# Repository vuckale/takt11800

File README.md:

# takt11800 - Compaq MX 11800 QMK/VIA Replacement PCB

Sponsored by PCBWay - [Read More](#pcbway)

This project is a **drop-in replacement PCB** designed for the **Compaq MX 11800**, also known as the **Cherry G80-11800** a classic mechanical keyboard featuring **Cherry MX Brown switches** and an integrated **trackball**.

Originally designed for use in server rooms and rack-mounted setups, the MX 11800's **compact, space-saving layout** made it a go-to choice in enterprise environments.

### Project Features

- **Powered by QMK Firmware** – Fully customizable keymaps, layers, macros, and lighting effects.
- **VIA Support** – Seamless configuration through the user-friendly VIA interface.
- **Trackball Support** – Full functionality for the integrated pointing device.
- **Drop-In Compatible** – No case modifications required. Designed to fit directly into the original shell and work with original components.
- **USB-C Connectivity** – Modern convenience and reliability.

### Known Issues

During testing, the integrated trackball worked reliably with some MX 11800 variants (based on testing with a single German layout unit), but showed intermittent or unreliable behavior on others (such as international-layout versions). In some cases, the trackball would work inconsistently or fail to initialize.

At the time of writing, no reliable software solution has been found. Based on the observed behavior and the available hardware information, it is suspected that this may be related to a voltage level mismatch. The MCU operates at 3.3 V logic, while the original trackball assembly may expect 5 V logic levels. This has not yet been conclusively confirmed and remains under investigation.

A revised PCB is planned to address this potential issue at the hardware level. Until then, builders should be aware that trackball functionality may vary depending on the specific keyboard and trackball assembly used.

### BOM and CPL Orientation

The included BOM (Bill of Materials) and CPL (Component Placement List) are provided for orientation purposes. Depending on the assembly options selected and any variations in components, you may need to adjust these files when placing your order to ensure correct assembly.

### Why This Project?

The original MX 11800 has aged gracefully, but its internals were due for a modern upgrade. This replacement PCB brings this legendary board into the modern era while preserving its unique charm and functionality.

Whether you're a retro keyboard enthusiast, a server admin with a soft spot for classic gear, or just someone who loves trackball keyboards, this project gives new life to an iconic piece of hardware.

# Layout

## Default Layout

This PCB supports multiple layout options. The previous image shows the default layout with colored keys and marked unit sizes that support alternate layouts. The default layout represents the configuration the keyboard is most commonly found in: ANSI enter with a 2.25u enter key, stepped caps lock, and a winkeyless 7u bottom row.

## Extended Layout

The extended layout adds support for additional four bottom row variations, which are marked on the image with the letters b–e. For easier assembly, these are also labeled on the PCB itself, with unit sizes marked next to the switch holes and a–e marked on the stabilizer holes. Additionally, the extended layout supports a non-stepped caps lock key, ISO enter, split left shift and a backspace and 2u shift that can be split into two 1u keys. The numpad can also be converted into a full 1u macropad.

## PCB Overview

## PCBWay

### Ordering Process

PCBWay made prototyping this PCB straightforward and easy. Their intuitive, beginner-friendly ordering process took all the guesswork out of manufacturing. I was impressed by how smoothly everything went, even on my first try. If you're curious to check it out or replicate the build, all the necessary files are neatly organized in the Fabrication Folder of this repository.

Following the steps on their interface, placing an order with PCBWay was easy. After uploading the Gerber .zip file, the platform pre-filled many default values suitable for my 2-layer PCB, simplifying the process significantly. The only manual customization I initially made was changing the solder mask color to black—a purely aesthetic choice. However, PCBWay offers a wide range of specification options for those who want more control.

You can choose between single pieces, customer-designed panels, or panels assembled by PCBWay, and even combine different PCB designs within a single panel. Layer configurations are highly flexible, ranging from 1 up to 14 layers, with support for advanced materials like FR-4, Aluminum, and Rogers for high-frequency or thermal applications. PCB thickness can be set anywhere from 0.2 mm up to 3.2 mm, and you can define track/spacing resolutions as fine as 3/3 mil. For higher durability or signal performance, different finished copper weights are also available—ranging from bare copper to 12 oz Cu.

Solder mask colors include not only standard options like green, red, and blue, but also premium finishes like matte black and matte green. Silkscreen printing supports multiple colors (white, black, yellow) and even UV multi-color printing. Additional advanced options include edge connectors, various surface finishes like ENIG, immersion silver, and ENEPIG, and via treatments such as tenting, plugging, or open vias.

You also have the option to remove PCBWay's product number for a small fee, specify custom FR4-TG ratings, and opt for specialized features like castellated holes, edge plating, or impedance control. With all these configuration options, PCBWay caters not only to hobbyists but also to professionals needing precise and high-performance PCBs.

For assembly, PCBWay provides a flexible set of options tailored to different needs: you can go with full turnkey assembly, where they source and solder everything; kitted/consigned, where you supply all the parts; or a combo option, where you send some components and let them handle the rest. 

For this project, I went with the full turnkey assembly—PCBWay not only assembled the boards but also sourced all the required components for me. This saved a huge amount of time and hassle, especially for parts that are hard to track down or have long lead times.

They also offer additional customization, like choosing whether to assemble single boards or panelized PCBs (recommended if you're doing runs of 20+ boards or working with small form factors), selecting top, bottom, or dual-sided assembly, and even specifying if you'd like to allow substitute components made in China—which I found useful for speeding up lead times without compromising quality.

Overall, their assembly service felt like a huge win—it was smooth, efficient, and let me focus entirely on design while they took care of the heavy lifting.

To do this, simply check the assembly option and fill in the necessary values as shown:

After clicking "Save to Cart," you can upload the BOM, CPL, and component placement orientation files to complete your order.

After placing the order, I had frequent and helpful communication with their engineering team, who reached out to clarify a few design decisions and even helped me correct some mistakes in my Gerber files. I really appreciated how responsive and collaborative they were—it felt like working with a partner, not just a service provider.

One particularly thoughtful touch was that before final assembly and shipping, they sent me high-resolution photos of the finished PCBs for confirmation. This gave me a last opportunity to visually inspect the boards and ensure everything looked right—a great quality-control step that added to my confidence in the process.

Throughout production, PCBWay provides visual order tracking on their website, which shows exactly where your order is at every stage—file review, fabrication, solder mask, silkscreen, assembly, testing, and packaging. It’s clearly laid out and updated in real time, which made the waiting process far less stressful.

The total turnaround time was about two weeks, which included fabrication, full assembly, and component sourcing. When the package arrived, it was clear that shipping was handled with care: each board was sealed in an anti-static bag, then carefully wrapped with protective shrink wrap and cushioning to prevent any damage during transit.

Overall, the combination of attentive support, visual transparency, and high-quality results made the whole experience smooth and satisfying. I wouldn’t hesitate to work with them again on future prototypes.

### Quality

This is where PCBWay truly shines. I was impressed by the overall PCB quality—the solder mask is perfectly uniform and consistent throughout. In my design, I included both silkscreen text and exposed copper text by selectively removing the top solder mask, and both came out flawless, with crisp details and no smudging or misalignment.

The components—including the MCU, SMD resistors, capacitors, and others—are perfectly placed, with flawless solder joints even on the tiniest parts. I’ll let the image speak for itself.

The plated through-holes on this PCB are clean, well-aligned, and have excellent copper coverage—perfect for reliable soldering. 

### Assembly

After soldering the switches and plugging in the trackball, all that was left was flashing the firmware. The STM32 chips come pre-flashed with a bootloader, so once connected to the PC, holding the BOOT switch and tapping NRST puts the board into flashing mode—simple as that.

The build includes 105 switches, and for a standard ISO layout, it uses 6× 2u stabilizers and 1× 7u stabilizer, though this may vary depending on the chosen layout.

### Final Words

Overall, working with PCBWay was a smooth and satisfying experience. The ordering process was easy, communication was fast and helpful, and the visual tracking kept me updated every step of the way. With a quick two-week turnaround, high-quality fabrication, flawless assembly, and great attention to detail, PCBWay delivered a professional result I’d gladly rely on again.

## License

This project is licensed under the **CERN Open Hardware Licence Version 2 - Strongly Reciprocal (CERN-OHL-S)**.

You are free to use, study, modify, and distribute the design files and products based on them, as long as any distributed modifications or derivative works are also released under the same license.

For the full license text, see the [LICENSE](LICENSE) file in this repository or visit the [official CERN OHL v2 page](https://gitlab.com/ohwr/project/cernohl/-/wikis/uploads/b236492596cfc91c12def7d50bbf7da0/cern_ohl_s_v2.pdf).

(C) 2025 [Aleksandar Vuckovic]

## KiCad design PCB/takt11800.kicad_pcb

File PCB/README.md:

# This is **Work In Progress**

Required **[Daughterboard repository](https://github.com:vuckale/va11800-daughterboard)**

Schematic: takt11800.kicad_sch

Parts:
BZ1: Buzzer; PinSocket_1x02_P2.00mm_Vertical
C8, C9: 1uF; Capacitor_0402; LCSC C52923
C10, C11, C13, C16: 100nF; Capacitor_0402; MPN CL05B104KB54PNC; LCSC C307331
C12, C17: 4.7uF; Capacitor_0402; MPN CL05A475MP5NRNC; LCSC C23733
C14: 10nF; Capacitor_0402; MPN CL05B103KB5NNNC; LCSC C15195
C15: 1uF; Capacitor_0402; MPN CL05A105KA5NQNC; LCSC C52923
C18: 100nF; Capacitor_0402; LCSC C307331
D1, D2, D3, D4, D5, D6, D7, D8, D9, D10, D11, D12, D13, D14, D15, D16, D17, D18, D19, D20, D21, D22, D23, D24, D25, D26, D27, D28, D29, D30, D31, D32, D33, D34, D35, D36, D37, D38, D39, D40, D41, D42, D43, D44, D45, D46, D47, D48, D49, D50, D51, D52, D53, D54, D56, D57, D58, D59, D60, D61, D62, D64, D65, D66, D67, D68, D69, D70, D72, D73, D74, D75, D76, D77, D78, D79, D80, D81, D82, D83, D84, D85, D86, D87, D88, D89, D90, D91, D92, D93, D94, D95, D96, D97, D98, D99, D100, D101, D102, D103, D104, D105, D106, D107, D108, D109, D110, D111, D112, D113, D114: D_Small; Diode-dual; LCSC C115103
D55, D63, D71: LED; LED_D2.00mm
F1: 500mA; Fuse_0603; LCSC C210357
H1, H2, H3, H4, H5: MountingHole; MountingHole_3.2mm_M3
J1: Conn_01x05; PinHeader_1x05_P2.54mm_Vertical
J2: USB4800-03-A; CONN_USB4800_GCT
J4: Conn_01x05_Pin; PinHeader_1x05_P2.00mm_Vertical
NUBS-key1: MX-NoLED; MXOnly-1U-NoLED
NUHS-key1: MX-NoLED; MXOnly-1U-NoLED
R1, R2, R3: 0.22K; Resistor
R4, R5: 10K; Resistor_0402
R6: 10k; Resistor_0402; LCSC C25744
R7, R8: 5.1k; Resistor_0402; LCSC C25905
SW1: BOOT; Button_TL3342; LCSC C115351
SW2: NRST; Button_TL3342; LCSC C115351
U1: STM32F072CBT6; Package_LQFP-48_7x7mm_P0.5; LCSC C81720
U2: CD74HC4067SM; SSOP-24_5.3x8.2mm_P0.65mm
U3: XC6206; Voltage_SOT-23; LCSC C5446
U4: USBLC6-2SC6; ESD_SOT-23-6; LCSC C2827654
a-key1: MX-NoLED; MXOnly-1U-NoLED
apostrophe-key1: MX-NoLED; MXOnly-1U-NoLED
arrow-down-key1: MX-NoLED; MXOnly-1U-NoLED
arrow-left-key1: MX-NoLED; MXOnly-1U-NoLED
arrow-right-key1: MX-NoLED; MXOnly-1U-NoLED
arrow-up-key1: MX-NoLED; MXOnly-1U-NoLED
b-key1: MX-NoLED; MXOnly-1U-NoLED
backspace1-key1, backspace3-key1: MX-NoLED; MXOnly-1U-NoLED
backspace2-key1: MX-NoLED; MXOnly-2U-ReversedStabilizers-NoLED
c-key1: MX-NoLED; MXOnly-1U-NoLED
capslock-standard-key1: MX-NoLED; MXOnly-1.75U-NoLED
capslock-stepped-key1: MX-NoLED; MXOnly-1.25U-NoLED
comma-key1: MX-NoLED; MXOnly-1U-NoLED
delete-Key1: MX-NoLED; MXOnly-1U-NoLED
dot-key1: MX-NoLED; MXOnly-1U-NoLED
e-key1: MX-NoLED; MXOnly-1U-NoLED
end-Key1: MX-NoLED; MXOnly-1U-NoLED
enter-ANSI-key1: MX-NoLED; MXOnly-2.25U-NoLED
enter-ISO-key1: MX-NoLED; MXOnly-ISO-ReversedStabilizers-NoLED
equal-key1: MX-NoLED; MXOnly-1U-NoLED
escape-Key1: MX-NoLED; MXOnly-1U-NoLED
f1-Key1, f2-Key1, f3-Key1, f4-Key1, f5-Key1, f6-Key1, f7-Key1, f8-Key1, f9-Key1, f10-Key1, f11-Key1, f12-Key1: MX-NoLED; MXOnly-1U-NoLED
f-key1: MX-NoLED; MXOnly-1U-NoLED
g-key1: MX-NoLED; MXOnly-1U-NoLED
grave-key1: MX-NoLED; MXOnly-1U-NoLED
h-key1: MX-NoLED; MXOnly-1U-NoLED
home-Key1: MX-NoLED; MXOnly-1U-NoLED
i-key1: MX-NoLED; MXOnly-1U-NoLED
insert-Key1: MX-NoLED; MXOnly-1U-NoLED
j-key1: MX-NoLED; MXOnly-1U-NoLED
k-key1: MX-NoLED; MXOnly-1U-NoLED
key_d1: MX-NoLED; MXOnly-1U-NoLED
kp_#0-1U-left-key1, kp_#0-1U-right-key1, kp_#2-key1, kp_#2-key2, kp_#3-key1, kp_#4-key1, kp_#5-key1, kp_#6-key1, kp_#8-key1, kp_#9-key1: MX-NoLED; MXOnly-1U-NoLED
kp_#0-2U-key1: MX-NoLED; MXOnly-2U-ReversedStabilizers-NoLED
kp_#7-key1: MX_NoLED; MXOnly-1U-NoLED
kp_comma-key1: MX-NoLED; MXOnly-1U-NoLED
kp_divide-key1: MX-NoLED; MXOnly-1U-NoLED
kp_enter-1U-down-key1, kp_enter-1U-top-key1: MX-NoLED; MXOnly-1U-NoLED
kp_enter-2U-key1: MX-NoLED; MXOnly-2U-VerticalStabilizers-NoLED
kp_minus-key1: MX-NoLED; MXOnly-1U-NoLED
kp_plus1-key1: MX-NoLED; MXOnly-2U-VerticalStabilizers-NoLED
kp_plus2-key1: MX-NoLED; MXOnly-1U-NoLED
kp_plus-1U-down-key1: MX-NoLED; MXOnly-1U-NoLED
kp_times-key1: MX-NoLED; MXOnly-1U-NoLED
l-key1: MX-NoLED; MXOnly-1U-NoLED
left-mod1-1.5U-key1, left-mod2-1.5U-key1: MX-NoLED; MXOnly-1.5U-NoLED
left-mod1-1.25U-key1, left-mod2-1.25U-key1, left-mod3-1.25U-key1: MX-NoLED; MXOnly-1.25U-NoLED
left-mod1-1U-key1, left-mod2-1U-key1, left-mod3-1U-key1: MX-NoLED; MXOnly-1U-NoLED
left_shift-1.25U-key1: MX-NoLED; MXOnly-1.25U-NoLED
left_shift-2.25U-key1: MX-NoLED; MXOnly-2.25U-NoLED
leftbrace-key1: MX-NoLED; MXOnly-1U-NoLED
m-key1: MX-NoLED; MXOnly-1U-NoLED
minus-key1: MX-NoLED; MXOnly-1U-NoLED
n0, n1, n2, n3, n4, n5, n6, n7, n8, n9: MX-NoLED; MXOnly-1U-NoLED
n-key1: MX-NoLED; MXOnly-1U-NoLED
numlock-Key1: MX-NoLED; MXOnly-1U-NoLED
o-key1: MX-NoLED; MXOnly-1U-NoLED
p-key1: MX-NoLED; MXOnly-1U-NoLED
pagedown-Key1: MX-NoLED; MXOnly-1U-NoLED
pageup-Key1: MX-NoLED; MXOnly-1U-NoLED
pause-Key1: MX-NoLED; MXOnly-1U-NoLED
pipe-key1: MX-NoLED; MXOnly-1.5U-NoLED
print-Key1: MX-NoLED; MXOnly-1U-NoLED
q-key1: MX-NoLED; MXOnly-1U-NoLED
r-key1: MX-NoLED; MXOnly-1U-NoLED
right-mod1-1.5U-key1, right-mod2-1.5U-key1: MX-NoLED; MXOnly-1.5U-NoLED
right-mod1-1.25U-key1, right-mod2-1.25U-key1, right-mod3-1.25U-key1: MX-NoLED; MXOnly-1.25U-NoLED
right-mod1-1U-key1, right-mod2-1U-key1, right-mod3-1U-key1, right-mod4-1U-key1: MX-NoLED; MXOnly-1U-NoLED
right_shift-1U-left-key1, right_shift-1U-right-key1: MX-NoLED; MXOnly-1U-NoLED
right_shift-2U-key1: MX-NoLED; MXOnly-2U-NoLED
rightbrace-key1: MX-NoLED; MXOnly-1U-NoLED
s-key1: MX-NoLED; MXOnly-1U-NoLED
scroll_lock-Key1: MX-NoLED; MXOnly-1U-NoLED
semicolon-key1: MX-NoLED; MXOnly-1U-NoLED
slash-key1: MX-NoLED; MXOnly-1U-NoLED
space-6.25-C-key1, space-6.25U-B-key1: MX-NoLED; MXOnly-6.25U-NoLED
space-6U1: MX-NoLED; MXOnly-6U-Centered-NoLED
space-6U/7U-key1: MX-NoLED; MXOnly-7U-NoLED
t-key1: MX-NoLED; MXOnly-1U-NoLED
tab-key1: MX-NoLED; MXOnly-1.5U-NoLED
u-key1: MX-NoLED; MXOnly-1U-NoLED
v-key1: MX-NoLED; MXOnly-1U-NoLED
w-key1: MX-NoLED; MXOnly-1U-NoLED
x-key1: MX-NoLED; MXOnly-1U-NoLED
y-key1: MX-NoLED; MXOnly-1U-NoLED
z-key1: MX-NoLED; MXOnly-1U-NoLED

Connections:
+3.3V: C9.1, C10.2, C11.2, C12.2, C13.2, C14.2, C15.2, C16.2, C17.2, J1.5, R4.2, R5.2, SW1.1, U1.1 (VBAT), U1.9 (VDDA), U1.24 (VDD), U1.36 (VDDIO2), U1.48 (VDD), U2.24 (VCC), U3.2 (VO)
+5V: C8.1, F1.2, J4.3, U3.3 (VI)
/A9: U1.30 (PA9)
/A10: U1.31 (PA10)
/B2: U1.20 (PB2)
/BOOT0: R6.2, SW1.2, U1.44 (BOOT0)
/C14: U1.3 (PC14)
/C15: U1.4 (PC15)
/F0: U1.5 (PF0)
/F1: U1.6 (PF1)
/MCU_D+: U1.33 (PA12), U4.1 (I/O1)
/MCU_D-: U1.32 (PA11), U4.3 (I/O2)
/NRST: C18.2, SW2.2, U1.7 (NRST)
/USB_D+: J2.A6 (DP1), J2.B6 (DP2), U4.6 (I/O1)
/USB_D-: J2.A7 (DN1), J2.B7 (DN2), U4.4 (I/O2)
CLK: J4.4, R5.1, U1.10 (PA0)
CapsLock: R2.2, U1.21 (PB10)
DATA: J4.5, R4.1, U1.11 (PA1)
GND: BZ1.1 (+), C8.2, C9.2, C10.1, C11.1, C12.1, C13.1, C14.1, C15.1, C16.1, C17.1, C18.1, D55.1 (K), D63.1 (K), D71.1 (K), J1.1, J2.A1 (GND), J2.A12 (GND), J2.B1 (GND), J2.B12 (GND), J4.1, J4.2, R6.1, R7.2, R8.1, SW2.1, U1.8 (VSSA), U1.23 (VSS), U1.35 (VSS), U1.47 (VSS), U2.12 (GND), U2.15 (~E), U3.1 (GND), U4.2 (GND)
unnamed: D1.2 (A), left-mod1-1.5U-key1.2 (ROW), left-mod1-1.25U-key1.2 (ROW), left-mod1-1U-key1.2 (ROW)
unnamed: D2.2 (A), escape-Key1.2 (ROW)
unnamed: D4.2 (A), tab-key1.2 (ROW)
unnamed: D5.2 (A), capslock-standard-key1.2 (ROW), capslock-stepped-key1.2 (ROW)
unnamed: D6.2 (A), left_shift-1.25U-key1.2 (ROW), left_shift-2.25U-key1.2 (ROW)
unnamed: D7.2 (A), n1.2 (ROW)
unnamed: D8.2 (A), q-key1.2 (ROW)
unnamed: D9.2 (A), a-key1.2 (ROW)
unnamed: D10.2 (A), NUBS-key1.2 (ROW)
unnamed: D11.2 (A), left-mod2-1.5U-key1.2 (ROW), left-mod2-1.25U-key1.2 (ROW), left-mod2-1U-key1.2 (ROW)
unnamed: D12.2 (A), f1-Key1.2 (ROW)
unnamed: D13.2 (A), f7-Key1.2 (ROW)
unnamed: D14.2 (A), n2.2 (ROW)
unnamed: D15.2 (A), w-key1.2 (ROW)
unnamed: D16.2 (A), s-key1.2 (ROW)
unnamed: D17.2 (A), z-key1.2 (ROW)
unnamed: D18.2 (A), f2-Key1.2 (ROW)
unnamed: D19.2 (A), f8-Key1.2 (ROW)
unnamed: D20.2 (A), n3.2 (ROW)
unnamed: D21.2 (A), e-key1.2 (ROW)
unnamed: D22.2 (A), key_d1.2 (ROW)
unnamed: D23.2 (A), x-key1.2 (ROW)
unnamed: D24.2 (A), left-mod3-1.25U-key1.2 (ROW), left-mod3-1U-key1.2 (ROW)
unnamed: D25.2 (A), f3-Key1.2 (ROW)
unnamed: D26.2 (A), f9-Key1.2 (ROW)
unnamed: D27.2 (A), n4.2 (ROW)
unnamed: D28.2 (A), r-key1.2 (ROW)
unnamed: D29.2 (A), f-key1.2 (ROW)
unnamed: D30.2 (A), c-key1.2 (ROW)
unnamed: D31.2 (A), f4-Key1.2 (ROW)
unnamed: D32.2 (A), f10-Key1.2 (ROW)
unnamed: D33.2 (A), n5.2 (ROW)
unnamed: D34.2 (A), t-key1.2 (ROW)
unnamed: D35.2 (A), g-key1.2 (ROW)
unnamed: D36.2 (A), v-key1.2 (ROW)
unnamed: D37.2 (A), f5-Key1.2 (ROW)
unnamed: D38.2 (A), n6.2 (ROW)
unnamed: D39.2 (A), y-key1.2 (ROW)
unnamed: D40.2 (A), h-key1.2 (ROW)
unnamed: D41.2 (A), b-key1.2 (ROW)
unnamed: D42.2 (A), space-6.25-C-key1.2 (ROW), space-6.25U-B-key1.2 (ROW), space-6U1.2 (ROW), space-6U/7U-key1.2 (ROW)
unnamed: D43.2 (A), f11-Key1.2 (ROW)
unnamed: D44.2 (A), f6-Key1.2 (ROW)
unnamed: D45.2 (A), f12-Key1.2 (ROW)
unnamed: D46.2 (A), n7.2 (ROW)
unnamed: D47.2 (A), u-key1.2 (ROW)
unnamed: D48.2 (A), j-key1.2 (ROW)
unnamed: D49.2 (A), n-key1.2 (ROW)
unnamed: D50.2 (A), arrow-right-key1.2 (ROW)
unnamed: D51.2 (A), n8.2 (ROW)
unnamed: D52.2 (A), i-key1.2 (ROW)
unnamed: D53.2 (A), k-key1.2 (ROW)
unnamed: D54.2 (A), m-key1.2 (ROW)
unnamed: D55.2 (A), R1.1
unnamed: D56.2 (A), insert-Key1.2 (ROW)
unnamed: D57.2 (A), delete-Key1.2 (ROW)
unnamed: D58.2 (A), n9.2 (ROW)
unnamed: D59.2 (A), o-key1.2 (ROW)
unnamed: D60.2 (A), l-key1.2 (ROW)
unnamed: D61.2 (A), comma-key1.2 (ROW)
unnamed: D62.2 (A), arrow-down-key1.2 (ROW)
unnamed: D63.2 (A), R2.1
unnamed: D64.2 (A), home-Key1.2 (ROW)
unnamed: D65.2 (A), end-Key1.2 (ROW)
unnamed: D66.2 (A), n0.2 (ROW)
unnamed: D67.2 (A), p-key1.2 (ROW)
unnamed: D68.2 (A), semicolon-key1.2 (ROW)
unnamed: D69.2 (A), dot-key1.2 (ROW)
unnamed: D70.2 (A), right-mod1-1.25U-key1.2 (ROW), right-mod2-1U-key1.2 (ROW)
unnamed: D71.2 (A), R3.1
unnamed: D72.2 (A), slash-key1.2 (ROW)
unnamed: D73.2 (A), pageup-Key1.2 (ROW)
unnamed: D74.2 (A), pagedown-Key1.2 (ROW)
unnamed: D75.2 (A), minus-key1.2 (ROW)
unnamed: D76.2 (A), leftbrace-key1.2 (ROW)
unnamed: D77.2 (A), apostrophe-key1.2 (ROW)
unnamed: D78.2 (A), right-mod1-1.5U-key1.2 (ROW), right-mod2-1.25U-key1.2 (ROW), right-mod3-1U-key1.2 (ROW)
unnamed: D79.2 (A), equal-key1.2 (ROW)
unnamed: D80.2 (A), rightbrace-key1.2 (ROW)
unnamed: D81.2 (A), NUHS-key1.2 (ROW)
unnamed: D82.2 (A), print-Key1.2 (ROW)
unnamed: D83.2 (A), scroll_lock-Key1.2 (ROW)
unnamed: D85.2 (A), right-mod1-1U-key1.2 (ROW)
unnamed: D87.2 (A), backspace1-key1.2 (ROW), backspace2-key1.2 (ROW)
unnamed: D88.2 (A), right_shift-1U-left-key1.2 (ROW), right_shift-2U-key1.2 (ROW)
unnamed: D89.2 (A), right-mod2-1.5U-key1.2 (ROW), right-mod3-1.25U-key1.2 (ROW), right-mod4-1U-key1.2 (ROW)
unnamed: D90.2 (A), numlock-Key1.2 (ROW)
unnamed: D91.2 (A), kp_#7-key1.2 (ROW)
unnamed: D93.2 (A), pipe-key1.2 (ROW)
unnamed: D94.2 (A), enter-ANSI-key1.2 (ROW), enter-ISO-key1.2 (ROW)
unnamed: D95.2 (A), right_shift-1U-right-key1.2 (ROW)
unnamed: D96.2 (A), arrow-left-key1.2 (ROW)
unnamed: D97.2 (A), kp_divide-key1.2 (ROW)
unnamed: D98.2 (A), kp_#8-key1.2 (ROW)
unnamed: D99.2 (A), kp_comma-key1.2 (ROW)
unnamed: D100.2 (A), arrow-up-key1.2 (ROW)
unnamed: D101.2 (A), kp_times-key1.2 (ROW)
unnamed: D102.2 (A), kp_#9-key1.2 (ROW)
unnamed: D103.2 (A), kp_#4-key1.2 (ROW)
unnamed: D104.2 (A), kp_#6-key1.2 (ROW)
unnamed: D105.2 (A), kp_#2-key1.2 (ROW)
unnamed: D106.2 (A), kp_#3-key1.2 (ROW)
unnamed: D107.2 (A), kp_#0-1U-left-key1.2 (ROW), kp_#0-2U-key1.2 (ROW)
unnamed: D109.2 (A), kp_plus1-key1.2 (ROW), kp_plus2-key1.2 (ROW)
unnamed: D110.2 (A), kp_#5-key1.2 (ROW)
unnamed: D111.2 (A), kp_plus-1U-down-key1.2 (ROW)
unnamed: D112.2 (A), kp_#2-key2.2 (ROW)
unnamed: D113.2 (A), kp_enter-1U-top-key1.2 (ROW), kp_enter-2U-key1.2 (ROW)
unnamed: D114.2 (A), kp_#0-1U-right-key1.2 (ROW)
unnamed: J2.A5 (CC1), R7.1
unnamed: J2.B5 (CC2), R8.2
NumLock: R1.2, U1.22 (PB11)
SWCLK: J1.2, U1.37 (PA14)
SWDIO: J1.3, U1.34 (PA13)
SWO: J1.4, U1.39 (PB3)
ScrollLock: R3.2, U1.2 (PC13)
VBUS: F1.1, J2.A4 (VBUS), J2.A9 (VBUS), J2.B4 (VBUS), J2.B9 (VBUS), U4.5 (VBUS)
buzzer+: BZ1.2 (-), U1.38 (PA15)
col0: NUBS-key1.1 (COL), U2.9 (I0), a-key1.1 (COL), capslock-standard-key1.1 (COL), capslock-stepped-key1.1 (COL), escape-Key1.1 (COL), grave-key1.1 (COL), left-mod1-1.5U-key1.1 (COL), left-mod1-1.25U-key1.1 (COL), left-mod1-1U-key1.1 (COL), left-mod2-1.5U-key1.1 (COL), left-mod2-1.25U-key1.1 (COL), left-mod2-1U-key1.1 (COL), left_shift-1.25U-key1.1 (COL), left_shift-2.25U-key1.1 (COL), n1.1 (COL), q-key1.1 (COL), tab-key1.1 (COL)
col1: U2.8 (I1), e-key1.1 (COL), f1-Key1.1 (COL), f2-Key1.1 (COL), f7-Key1.1 (COL), f8-Key1.1 (COL), key_d1.1 (COL), left-mod3-1.25U-key1.1 (COL), left-mod3-1U-key1.1 (COL), n2.1 (COL), n3.1 (COL), s-key1.1 (COL), w-key1.1 (COL), x-key1.1 (COL), z-key1.1 (COL)
col2: U2.7 (I2), c-key1.1 (COL), f3-Key1.1 (COL), f4-Key1.1 (COL), f9-Key1.1 (COL), f10-Key1.1 (COL), f-key1.1 (COL), g-key1.1 (COL), n4.1 (COL), n5.1 (COL), r-key1.1 (COL), t-key1.1 (COL), v-key1.1 (COL)
col3: U2.6 (I3), b-key1.1 (COL), f5-Key1.1 (COL), f6-Key1.1 (COL), f11-Key1.1 (COL), f12-Key1.1 (COL), h-key1.1 (COL), j-key1.1 (COL), n6.1 (COL), n7.1 (COL), n-key1.1 (COL), space-6.25-C-key1.1 (COL), space-6.25U-B-key1.1 (COL), space-6U1.1 (COL), space-6U/7U-key1.1 (COL), u-key1.1 (COL), y-key1.1 (COL)
col4: U2.5 (I4), arrow-down-key1.1 (COL), arrow-right-key1.1 (COL), comma-key1.1 (COL), delete-Key1.1 (COL), i-key1.1 (COL), insert-Key1.1 (COL), k-key1.1 (COL), l-key1.1 (COL), m-key1.1 (COL), n8.1 (COL), n9.1 (COL), o-key1.1 (COL)
col5: U2.4 (I5), apostrophe-key1.1 (COL), dot-key1.1 (COL), end-Key1.1 (COL), home-Key1.1 (COL), leftbrace-key1.1 (COL), minus-key1.1 (COL), n0.1 (COL), p-key1.1 (COL), pagedown-Key1.1 (COL), pageup-Key1.1 (COL), right-mod1-1.5U-key1.1 (COL), right-mod1-1.25U-key1.1 (COL), right-mod2-1.25U-key1.1 (COL), right-mod2-1U-key1.1 (COL), right-mod3-1U-key1.1 (COL), semicolon-key1.1 (COL), slash-key1.1 (COL)
col6: NUHS-key1.1 (COL), U2.3 (I6), backspace1-key1.1 (COL), backspace2-key1.1 (COL), equal-key1.1 (COL), kp_enter-1U-down-key1.1 (COL), pause-Key1.1 (COL), print-Key1.1 (COL), right-mod1-1U-key1.1 (COL), right-mod2-1.5U-key1.1 (COL), right-mod3-1.25U-key1.1 (COL), right-mod4-1U-key1.1 (COL), right_shift-1U-left-key1.1 (COL), right_shift-2U-key1.1 (COL), rightbrace-key1.1 (COL), scroll_lock-Key1.1 (COL)
col7: U2.2 (I7), arrow-left-key1.1 (COL), arrow-up-key1.1 (COL), backspace3-key1.1 (COL), enter-ANSI-key1.1 (COL), enter-ISO-key1.1 (COL), kp_#7-key1.1 (COL), kp_#8-key1.1 (COL), kp_comma-key1.1 (COL), kp_divide-key1.1 (COL), numlock-Key1.1 (COL), pipe-key1.1 (COL), right_shift-1U-right-key1.1 (COL)
col8: U2.23 (I8), kp_#0-1U-left-key1.1 (COL), kp_#0-1U-right-key1.1 (COL), kp_#0-2U-key1.1 (COL), kp_#2-key1.1 (COL), kp_#2-key2.1 (COL), kp_#3-key1.1 (COL), kp_#4-key1.1 (COL), kp_#5-key1.1 (COL), kp_#6-key1.1 (COL), kp_#9-key1.1 (COL), kp_enter-1U-top-key1.1 (COL), kp_enter-2U-key1.1 (COL), kp_minus-key1.1 (COL), kp_plus1-key1.1 (COL), kp_plus2-key1.1 (COL), kp_plus-1U-down-key1.1 (COL), kp_times-key1.1 (COL)
encA1_row5_d: D3.2 (A), grave-key1.2 (ROW)
encA2_row5_d: D92.2 (A), backspace3-key1.2 (ROW)
encB_row1_d: D86.2 (A), pause-Key1.2 (ROW)
encC1_row0_d: D108.2 (A), kp_minus-key1.2 (ROW)
encC2_row11_d: D84.2 (A), kp_enter-1U-down-key1.2 (ROW)
row0: D2.1 (K), D18.1 (K), D31.1 (K), D44.1 (K), D64.1 (K), D82.1 (K), D97.1 (K), D108.1 (K), U1.15 (PA5)
row1: D12.1 (K), D25.1 (K), D37.1 (K), D56.1 (K), D73.1 (K), D86.1 (K), D90.1 (K), D101.1 (K), U1.12 (PA2)
row2: D19.1 (K), D32.1 (K), D45.1 (K), D65.1 (K), D98.1 (K), D109.1 (K), U1.14 (PA4)
row3: D13.1 (K), D26.1 (K), D43.1 (K), D57.1 (K), D74.1 (K), D83.1 (K), D91.1 (K), D102.1 (K), U1.13 (PA3)
row4: D7.1 (K), D20.1 (K), D33.1 (K), D46.1 (K), D58.1 (K), D75.1 (K), D87.1 (K), D110.1 (K), U1.25 (PB12)
row5: D3.1 (K), D14.1 (K), D27.1 (K), D38.1 (K), D51.1 (K), D66.1 (K), D79.1 (K), D92.1 (K), D103.1 (K), U1.26 (PB13)
row6: D8.1 (K), D21.1 (K), D34.1 (K), D47.1 (K), D59.1 (K), D76.1 (K), D93.1 (K), D104.1 (K), U1.27 (PB14)
row7: D4.1 (K), D15.1 (K), D28.1 (K), D39.1 (K), D52.1 (K), D67.1 (K), D80.1 (K), D111.1 (K), U1.28 (PB15)
row8: D9.1 (K), D22.1 (K), D35.1 (K), D48.1 (K), D60.1 (K), D77.1 (K), D94.1 (K), D112.1 (K), U1.29 (PA8)
row9: D5.1 (K), D16.1 (K), D29.1 (K), D40.1 (K), D53.1 (K), D68.1 (K), D81.1 (K), D105.1 (K), U1.19 (PB1)
row10: D10.1 (K), D23.1 (K), D36.1 (K), D49.1 (K), D61.1 (K), D72.1 (K), D88.1 (K), D99.1 (K), D106.1 (K), U1.18 (PB0)
row11: D6.1 (K), D17.1 (K), D30.1 (K), D41.1 (K), D54.1 (K), D69.1 (K), D84.1 (K), D95.1 (K), D113.1 (K), U1.46 (PB9)
row12: D11.1 (K), D62.1 (K), D78.1 (K), D85.1 (K), D96.1 (K), D107.1 (K), U1.17 (PA7)
row13: D1.1 (K), D24.1 (K), D42.1 (K), D50.1 (K), D70.1 (K), D89.1 (K), D100.1 (K), D114.1 (K), U1.16 (PA6)
s0: U1.41 (PB5), U2.10 (S0)
s1: U1.42 (PB6), U2.11 (S1)
s2: U1.45 (PB8), U2.14 (S2)
s3: U1.43 (PB7), U2.13 (S3)
sig: U1.40 (PB4), U2.1 (COM)

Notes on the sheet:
Other
LEDs
Controller
PS/2 Interface
Power Flags
Voltage Step Down
USB-C
MUX
Buzzer
SWD Interface
ESD Protection
Mounting Holes
Connector
STM32F072CBT6
Bootloader Button
Decoupling Capacitors

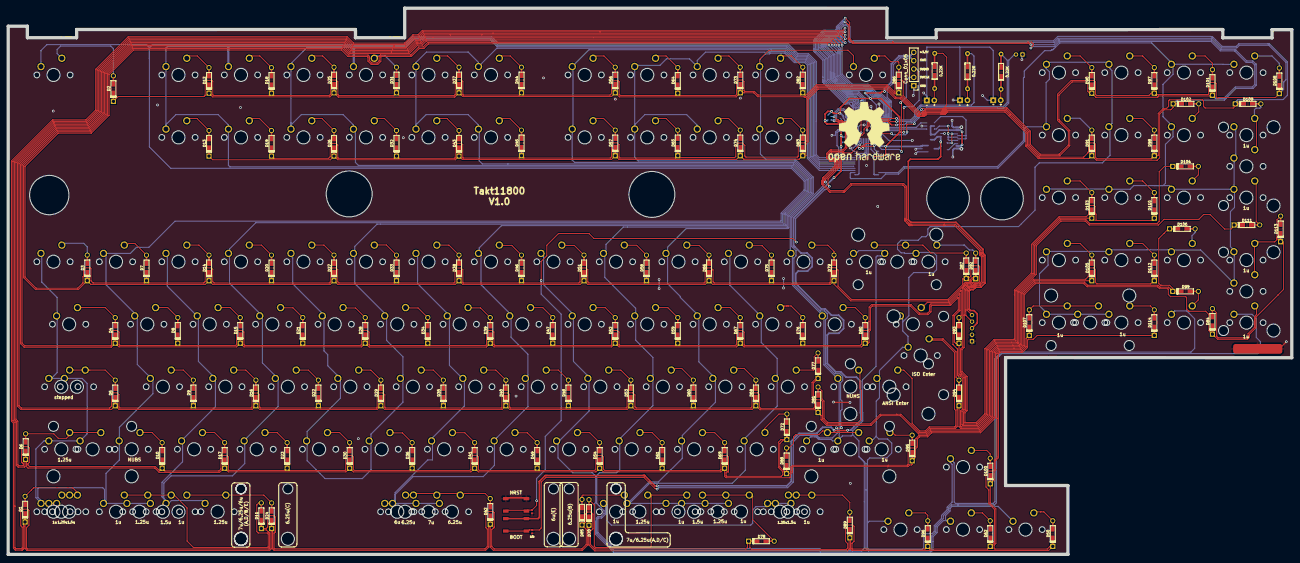
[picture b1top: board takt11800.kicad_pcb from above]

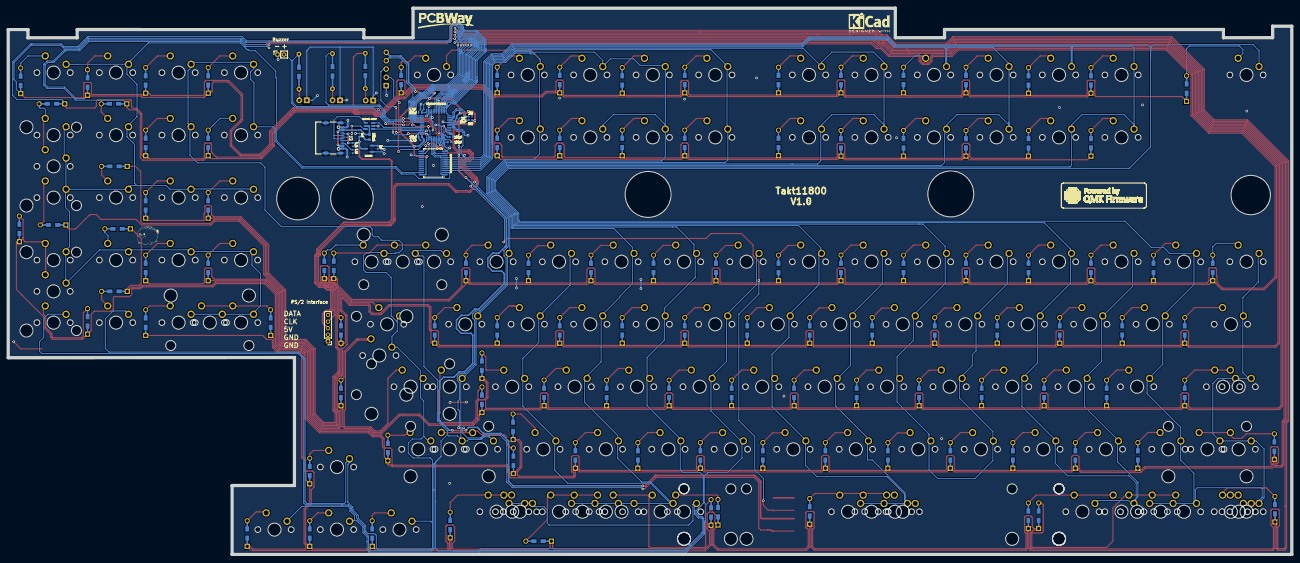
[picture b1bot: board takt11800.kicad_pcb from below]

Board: 2 copper layers, 391.2 x 166.5 mm, 282 parts (28 on the bottom side), 163 nets.

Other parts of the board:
Kicad: KiCad-Logo2_5mm_SilkScreen

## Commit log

2025-04-25 Refactor PCB and firmware structure; update docs, assets, and remove legacy files
2025-04-26 optimize image size
2025-04-26 fix readme
2025-05-30 update ps2 code
2025-07-03 update USB-C footprint; adjust arrow keys position; cleanup libraries
2025-12-21 update Readme, add BOM and CPL
2025-12-21 fix BOM csv formatting
